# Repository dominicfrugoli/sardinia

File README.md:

<br/>
<div align="center">

<h3 align="center">Sardinia</h3>
<p align="center">
Sampler based on the Electrosmith Daisy platform

</p>
</div>

## About The Project

[Notion Project Homepage](https://fenidesign.notion.site/Sardinia-Independent-Project-24255e64caba44d3b6232d27743844be?pvs=4)

Sardinia is the codename for a sampler that is currently being built by me for an Independent Project during my senior year at Columbia College Chicago. It uses the Electrosmith Daisy platform and is an exercise for me to venture into the world of product design.

This independent project is called "The Product Design Process for Electronic Instruments" and was pitched by myself specifically to give myself experience in the process of the full production of an audio hardware device. This means starting at research, then going through every stage of production and design to end up with a final product. There is a large emphasis on the process and showing future companies that I understand somewhat what it takes.
### Built With

- [Daisy Seed](https://electro-smith.com/products/daisy-seed)
- [libDaisy](https://github.com/electro-smith/libDaisy)
- [DaisySP](https://github.com/electro-smith/DaisySP)
- [KiCad](https://www.kicad.org/)
- [Fusion 360](https://www.autodesk.com/products/fusion-360/)
## Roadmap

##### Weeks 1-5 | Ideation and Programming

- Week 1
    - Come up with overall idea and mission statement for the instrument
    - Research DSP ideas and programming concepts needed
    - Gather ideas and inspiration from specific hardware
- Week 2 & 3
    - Start programming all DSP and hardware handling for instrument
    - Lots of iteration and testing will be needed
    - Research here is critical as well to get main audio concepts down
    - Daisy Examples will be main research source
    - Recording different iterations of the project will be great for documentation
- Week 4 & 5
    - Work on finalizing code and getting it to a point for implementation
    - Use daisy examples and others’ code to help with style guidance
    - Get friends to test out for playability and sound, as well as get ideas
    - Build a central repo for code which can be updated as needed
    - Coding doesn’t stop with this step, but it should be mostly done by now
    - Start recording breadboard schematics if time allows to make PCB design easier

#####  Weeks 6-10 | PCB and Hardware Design

- Week 6 & 7
    - Refresh KICAD skills with tutorials
    - Build out schematic for PCB in KICAD
    - Design PCB completely and order for testing in week 8 & 9
    - Case design will be important here to make sure layout works with PCB
    - Final component selection will take place here
- Week 8 & 9
    - Work on case design with cardboard PCB to test out everything
    - Decide on case material (likely 3D printed)
    - Build out specifics for case such as standoff points and strength areas
    - Allow case to have daisy in a place that is easily reprogrammed
    - Assemble and test PCBs once they arrive (make changes and reorder if necessary)
    - Finish working on design and model for case
- Week 10
    - Start putting together first prototype of instrument with printed PCB and case
    - Play with instrument musically and have others try
    - This is when a lot of testing can be done for the usability

#####  Weeks 11-15 | Manufacturing and Documentation

- Week 11
    - Finalize design of case and overall visual style of instrument
    - Work on process for assembling, as well as BOM and any other assembly materials
- Week 12 & 13
    - Work on customer documentation for instrument
    - Design manual for the user
    - Design packaging for the instrument
    - Work on advertising and marketing for it
- Week 14 & 15
    - Build final version of instrument to be shown and displayed
        - Maybe one fully complete and two hollow cases for ad campaign
    - Final write up and documentation for instrument
    - Add writeup to portfolio website
    - Present it to friends and professors
    - Any last requirements for Visda

## Contact

Dominic Frugoli - [Portfolio](https://www.dominicfrugoli.com/) - dominicfrugoli@gmail.com

Project Link: [Notion Page](https://fenidesign.notion.site/Sardinia-Independent-Project-24255e64caba44d3b6232d27743844be?pvs=4)
## Acknowledgments

- Dr. Visda Goudarzi

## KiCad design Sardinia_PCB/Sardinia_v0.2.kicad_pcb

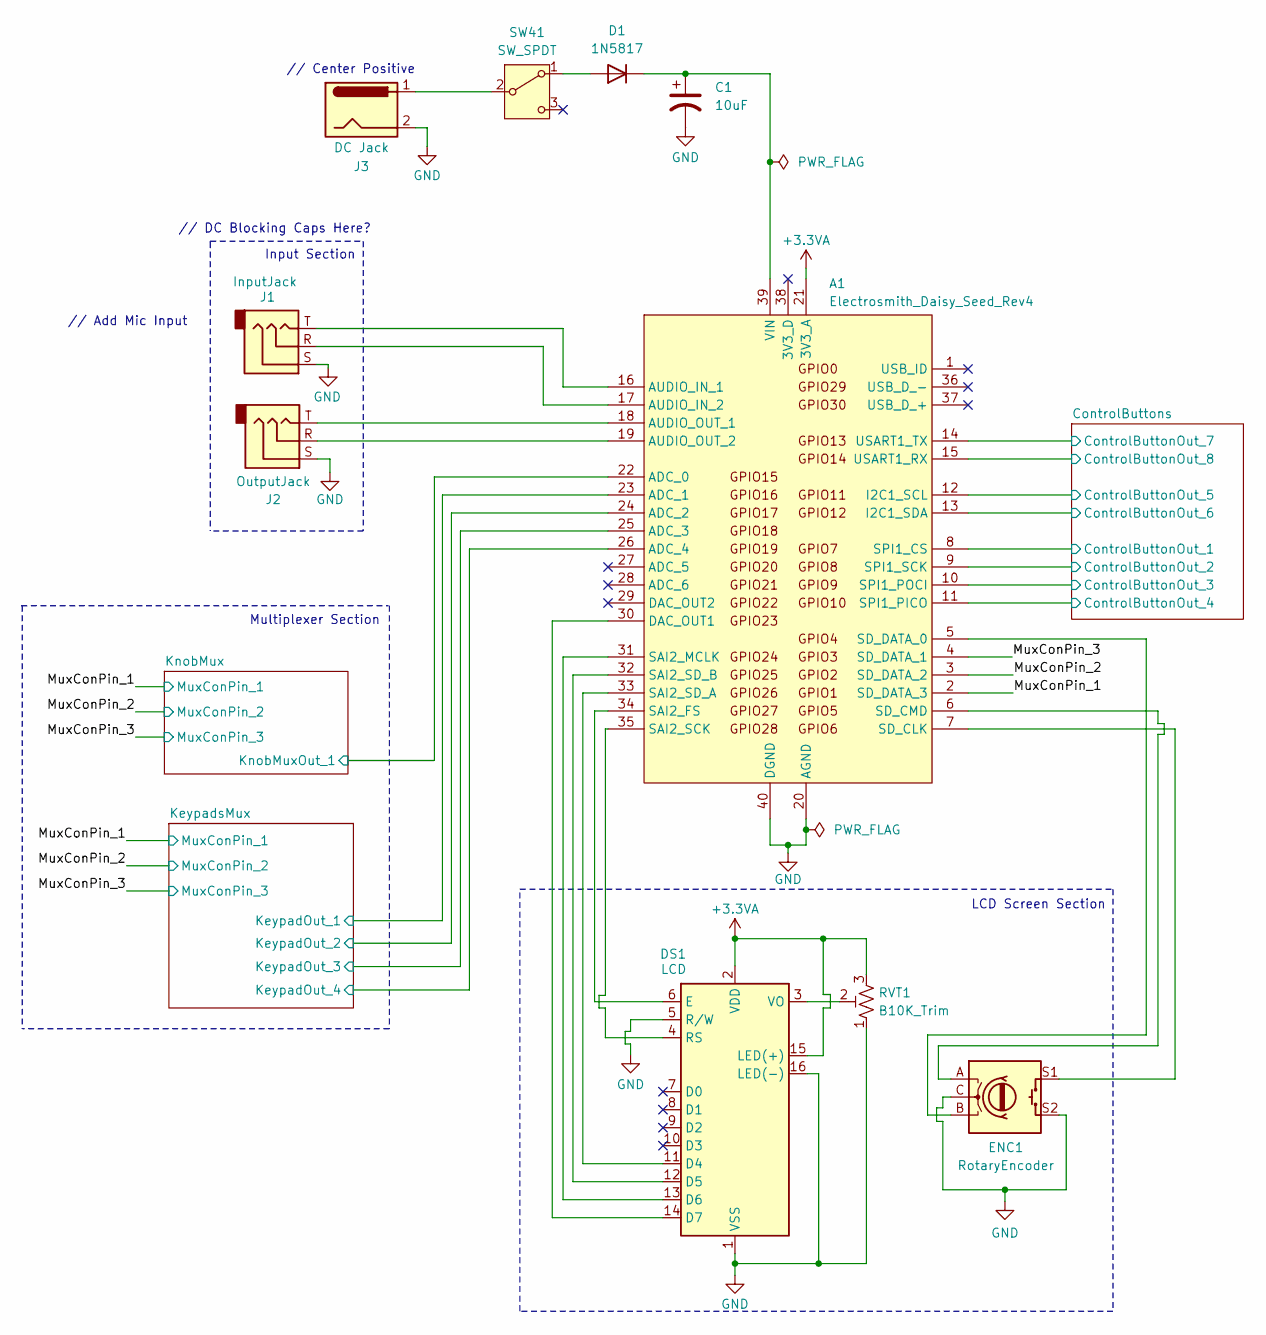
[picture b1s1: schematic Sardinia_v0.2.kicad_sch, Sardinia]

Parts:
A1: Electrosmith_Daisy_Seed_Rev4; Electrosmith_Daisy_Seed
C1: 10uF; CP_Radial_D5.0mm_P2.50mm
D1: 1N5817; D_DO-41_SOD81_P7.62mm_Horizontal
DS1: LCD; WC1602A
ENC1: RotaryEncoder; RotaryEncoder_Alps_EC11E-Switch_Vertical_H20mm
J1: InputJack; Jack_6.35mm_Neutrik_NMJ6HCD2_Horizontal
J2: OutputJack; Jack_6.35mm_Neutrik_NMJ6HCD2_Horizontal
J3: DC Jack; BarrelJack_Horizontal
RVT1: B10K_Trim; Potentiometer_Runtron_RM-065_Vertical
SW41: SW_SPDT; JST_PH_B3B-PH-K_1x03_P2.00mm_Vertical

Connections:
+3.3VA: A1.21 (3V3_A), DS1.2 (VDD), DS1.15 (LED(+)), RVT1.3; also elsewhere on the board
/ControlButtons/ControlButtonOut_1: A1.8 (SPI1_CS); also elsewhere on the board
/ControlButtons/ControlButtonOut_2: A1.9 (SPI1_SCK); also elsewhere on the board
/ControlButtons/ControlButtonOut_3: A1.10 (SPI1_POCI); also elsewhere on the board
/ControlButtons/ControlButtonOut_4: A1.11 (SPI1_PICO); also elsewhere on the board
/ControlButtons/ControlButtonOut_5: A1.12 (I2C1_SCL); also elsewhere on the board
/ControlButtons/ControlButtonOut_6: A1.13 (I2C1_SDA); also elsewhere on the board
/ControlButtons/ControlButtonOut_7: A1.14 (USART1_TX); also elsewhere on the board
/ControlButtons/ControlButtonOut_8: A1.15 (USART1_RX); also elsewhere on the board
/KeypadsMux/KeypadOut_1: A1.23 (ADC_1); also elsewhere on the board
/KeypadsMux/KeypadOut_2: A1.24 (ADC_2); also elsewhere on the board
/KeypadsMux/KeypadOut_3: A1.25 (ADC_3); also elsewhere on the board
/KeypadsMux/KeypadOut_4: A1.26 (ADC_4); also elsewhere on the board
/KnobMux/KnobMuxOut_1: A1.22 (ADC_0); also elsewhere on the board
/MuxConPin_1: A1.2 (SD_DATA_3); also elsewhere on the board
/MuxConPin_2: A1.3 (SD_DATA_2); also elsewhere on the board
/MuxConPin_3: A1.4 (SD_DATA_1); also elsewhere on the board
GND: A1.20 (AGND), A1.40 (DGND), C1.2, DS1.1 (VSS), DS1.5 (R/W), DS1.16 (LED(-)), ENC1.C, ENC1.S2, J1.S, J2.S, J3.2, RVT1.1; also elsewhere on the board
unnamed: A1.16 (AUDIO_IN_1), J1.T
unnamed: A1.17 (AUDIO_IN_2), J1.R
unnamed: A1.18 (AUDIO_OUT_1), J2.T
unnamed: A1.19 (AUDIO_OUT_2), J2.R
unnamed: A1.30 (DAC_OUT1), DS1.14 (D7)
unnamed: A1.34 (SAI2_FS), DS1.6 (E)
unnamed: A1.31 (SAI2_MCLK), DS1.13 (D6)
unnamed: A1.35 (SAI2_SCK), DS1.4 (RS)
unnamed: A1.33 (SAI2_SD_A), DS1.11 (D4)
unnamed: A1.32 (SAI2_SD_B), DS1.12 (D5)
unnamed: A1.7 (SD_CLK), ENC1.S1
unnamed: A1.6 (SD_CMD), ENC1.A
unnamed: A1.5 (SD_DATA_0), ENC1.B
unnamed: A1.39 (VIN), C1.1, D1.1 (K)
unnamed: D1.2 (A), SW41.1 (A)
unnamed: DS1.3 (VO), RVT1.2
unnamed: J3.1, SW41.2 (B)

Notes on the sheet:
// Center Positive
// Add Mic Input
LCD Screen Section
Input Section
// DC Blocking Caps Here?
Multiplexer Section

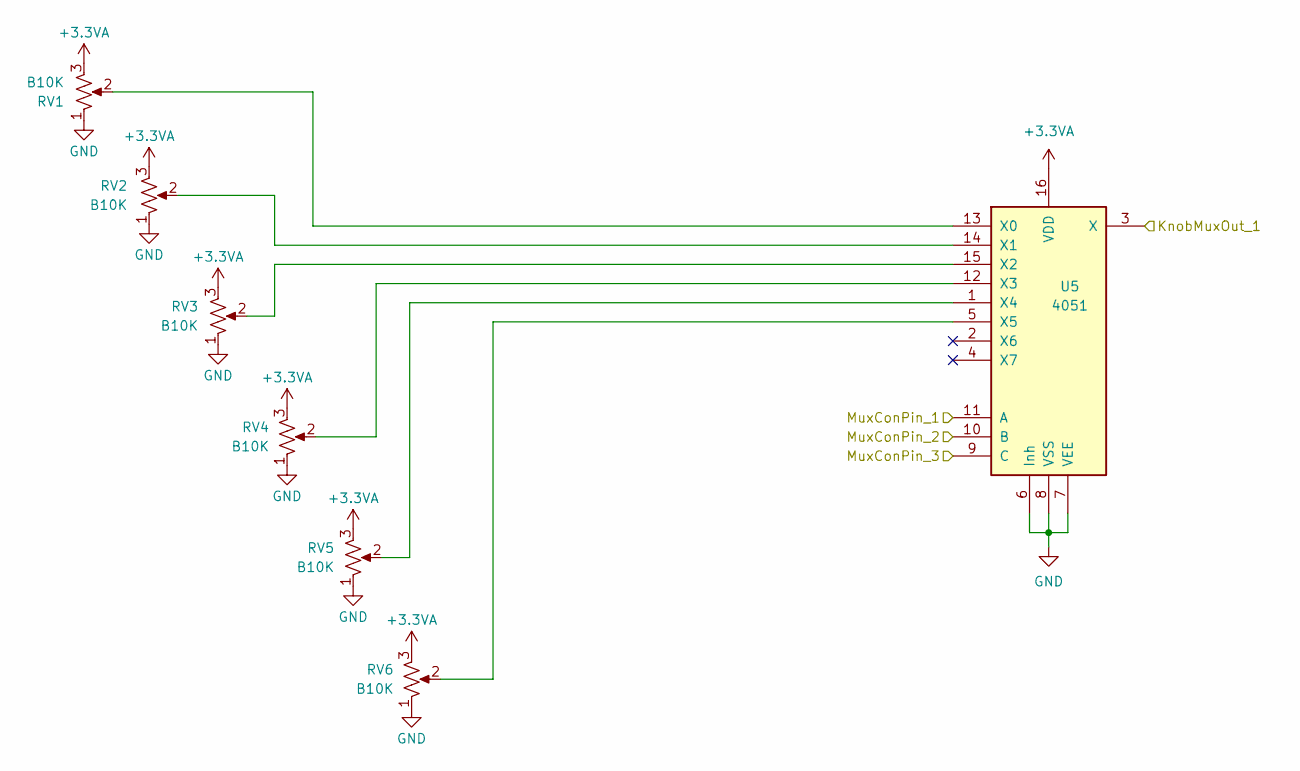
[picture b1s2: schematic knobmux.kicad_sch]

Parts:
RV1, RV2, RV3, RV4, RV5, RV6: B10K; Potentiometer_Alpha_RD901F-40-00D_Single_Vertical
U5: 4051; DIP-16_W7.62mm_LongPads

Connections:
+3.3VA: RV1.3, RV2.3, RV3.3, RV4.3, RV5.3, RV6.3, U5.16 (VDD); also elsewhere on the board
/KnobMux/KnobMuxOut_1: U5.3 (X); also elsewhere on the board
/MuxConPin_1: U5.11 (A); also elsewhere on the board
/MuxConPin_2: U5.10 (B); also elsewhere on the board
/MuxConPin_3: U5.9 (C); also elsewhere on the board
GND: RV1.1, RV2.1, RV3.1, RV4.1, RV5.1, RV6.1, U5.6 (Inh), U5.7 (VEE), U5.8 (VSS); also elsewhere on the board
unnamed: RV1.2, U5.13 (X0)
unnamed: RV2.2, U5.14 (X1)
unnamed: RV3.2, U5.15 (X2)
unnamed: RV4.2, U5.12 (X3)
unnamed: RV5.2, U5.1 (X4)
unnamed: RV6.2, U5.5 (X5)

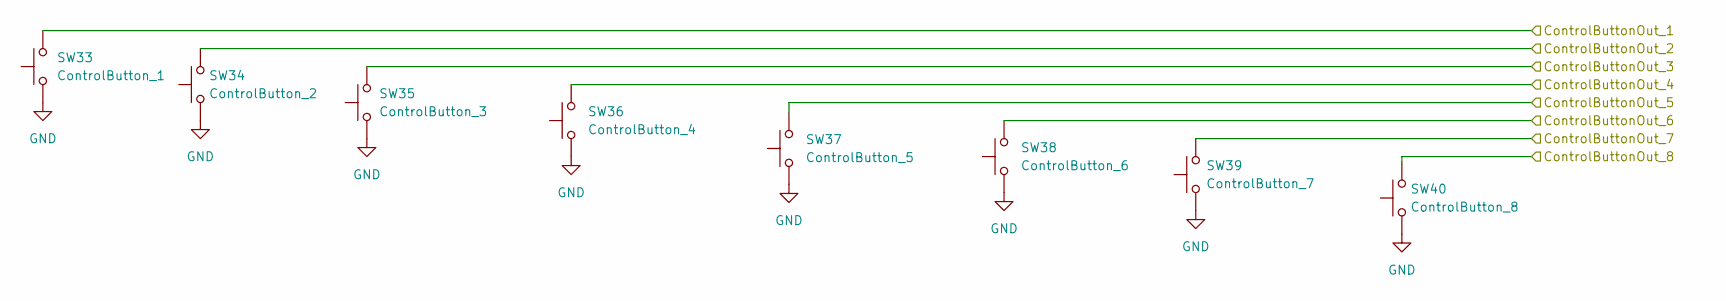
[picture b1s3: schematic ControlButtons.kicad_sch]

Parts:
SW33: ControlButton_1; SW_Cherry_MX_1.00u_PCB
SW34: ControlButton_2; SW_Cherry_MX_1.00u_PCB
SW35: ControlButton_3; SW_Cherry_MX_1.00u_PCB
SW36: ControlButton_4; SW_Cherry_MX_1.00u_PCB
SW37: ControlButton_5; SW_Cherry_MX_1.00u_PCB
SW38: ControlButton_6; SW_Cherry_MX_1.00u_PCB
SW39: ControlButton_7; SW_Cherry_MX_1.00u_PCB
SW40: ControlButton_8; SW_Cherry_MX_1.00u_PCB

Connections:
/ControlButtons/ControlButtonOut_1: SW33.2; also elsewhere on the board
/ControlButtons/ControlButtonOut_2: SW34.2; also elsewhere on the board
/ControlButtons/ControlButtonOut_3: SW35.2; also elsewhere on the board
/ControlButtons/ControlButtonOut_4: SW36.2; also elsewhere on the board
/ControlButtons/ControlButtonOut_5: SW37.2; also elsewhere on the board
/ControlButtons/ControlButtonOut_6: SW38.2; also elsewhere on the board
/ControlButtons/ControlButtonOut_7: SW39.2; also elsewhere on the board
/ControlButtons/ControlButtonOut_8: SW40.2; also elsewhere on the board
GND: SW33.1, SW34.1, SW35.1, SW36.1, SW37.1, SW38.1, SW39.1, SW40.1; also elsewhere on the board

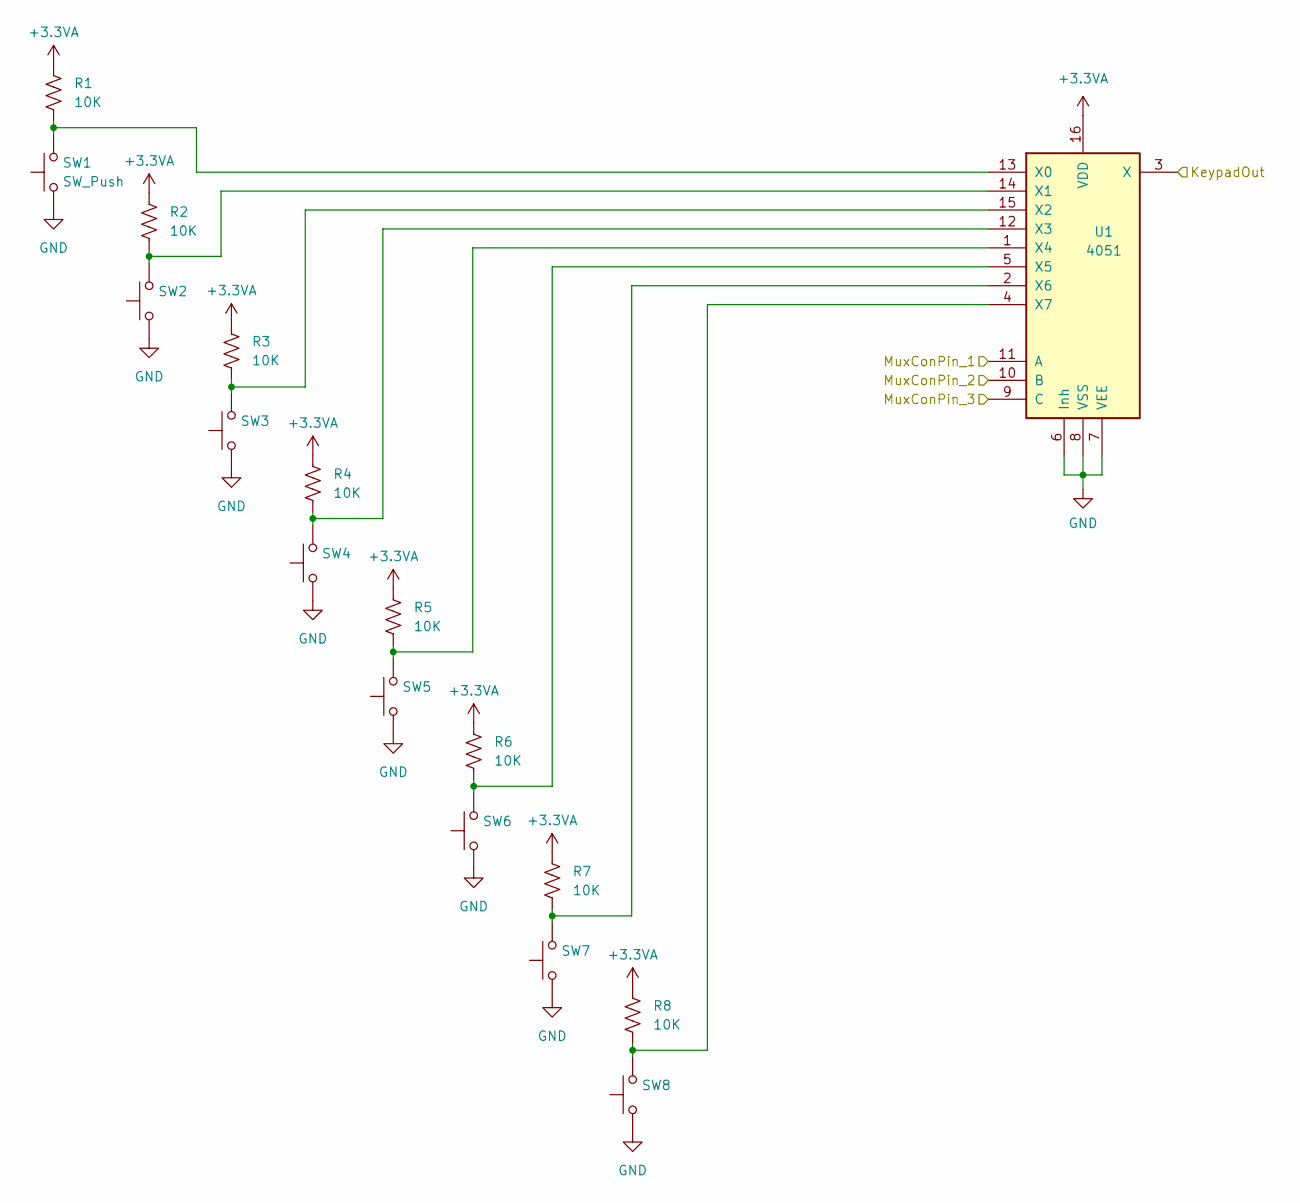
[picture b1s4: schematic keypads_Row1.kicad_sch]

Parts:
R1, R2, R3, R4, R5, R6, R7, R8: 10K; R_1206_3216Metric_Pad1.30x1.75mm_HandSolder
SW1, SW2, SW3, SW4, SW5, SW6, SW7, SW8: SW_Push; PG1350
U1: 4051; DIP-16_W7.62mm_LongPads

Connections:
+3.3VA: R1.1, R2.1, R3.1, R4.1, R5.1, R6.1, R7.1, R8.1, U1.16 (VDD); also elsewhere on the board
/KeypadsMux/KeypadOut_1: U1.3 (X); also elsewhere on the board
/MuxConPin_1: U1.11 (A); also elsewhere on the board
/MuxConPin_2: U1.10 (B); also elsewhere on the board
/MuxConPin_3: U1.9 (C); also elsewhere on the board
GND: SW1.1, SW2.1, SW3.1, SW4.1, SW5.1, SW6.1, SW7.1, SW8.1, U1.6 (Inh), U1.7 (VEE), U1.8 (VSS); also elsewhere on the board
unnamed: R1.2, SW1.2, U1.13 (X0)
unnamed: R2.2, SW2.2, U1.14 (X1)
unnamed: R3.2, SW3.2, U1.15 (X2)
unnamed: R4.2, SW4.2, U1.12 (X3)
unnamed: R5.2, SW5.2, U1.1 (X4)
unnamed: R6.2, SW6.2, U1.5 (X5)
unnamed: R7.2, SW7.2, U1.2 (X6)
unnamed: R8.2, SW8.2, U1.4 (X7)

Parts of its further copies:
R9, R10, R11, R12, R13, R14, R15, R16, R17, R18, R19, R20, R21, R22, R23, R24, R25, R26, R27, R28, R29, R30, R31, R32: 10K; R_1206_3216Metric_Pad1.30x1.75mm_HandSolder
SW9, SW10, SW11, SW12, SW13, SW14, SW15, SW16, SW17, SW18, SW19, SW20, SW21, SW22, SW23, SW24, SW25, SW26, SW27, SW28, SW29, SW30, SW31, SW32: SW_Push; PG1350
U2, U3, U4: 4051; DIP-16_W7.62mm_LongPads

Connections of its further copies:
+3.3VA: R9.1, R10.1, R11.1, R12.1, R13.1, R14.1, R15.1, R16.1, R17.1, R18.1, R19.1, R20.1, R21.1, R22.1, R23.1, R24.1, R25.1, R26.1, R27.1, R28.1, R29.1, R30.1, R31.1, R32.1, U2.16 (VDD), U3.16 (VDD), U4.16 (VDD); also elsewhere on the board
/KeypadsMux/KeypadOut_2: U2.3 (X); also elsewhere on the board
/KeypadsMux/KeypadOut_3: U3.3 (X); also elsewhere on the board
/KeypadsMux/KeypadOut_4: U4.3 (X); also elsewhere on the board
/MuxConPin_1: U2.11 (A), U3.11 (A), U4.11 (A); also elsewhere on the board
/MuxConPin_2: U2.10 (B), U3.10 (B), U4.10 (B); also elsewhere on the board
/MuxConPin_3: U2.9 (C), U3.9 (C), U4.9 (C); also elsewhere on the board
GND: SW9.1, SW10.1, SW11.1, SW12.1, SW13.1, SW14.1, SW15.1, SW16.1, SW17.1, SW18.1, SW19.1, SW20.1, SW21.1, SW22.1, SW23.1, SW24.1, SW25.1, SW26.1, SW27.1, SW28.1, SW29.1, SW30.1, SW31.1, SW32.1, U2.6 (Inh), U2.7 (VEE), U2.8 (VSS), U3.6 (Inh), U3.7 (VEE), U3.8 (VSS), U4.6 (Inh), U4.7 (VEE), U4.8 (VSS); also elsewhere on the board
unnamed: R9.2, SW9.2, U2.13 (X0)
unnamed: R10.2, SW10.2, U2.14 (X1)
unnamed: R11.2, SW11.2, U2.15 (X2)
unnamed: R12.2, SW12.2, U2.12 (X3)
unnamed: R13.2, SW13.2, U2.1 (X4)
unnamed: R14.2, SW14.2, U2.5 (X5)
unnamed: R15.2, SW15.2, U2.2 (X6)
unnamed: R16.2, SW16.2, U2.4 (X7)
unnamed: R17.2, SW17.2, U3.13 (X0)
unnamed: R18.2, SW18.2, U3.14 (X1)
unnamed: R19.2, SW19.2, U3.15 (X2)
unnamed: R20.2, SW20.2, U3.12 (X3)
unnamed: R21.2, SW21.2, U3.1 (X4)
unnamed: R22.2, SW22.2, U3.5 (X5)
unnamed: R23.2, SW23.2, U3.2 (X6)
unnamed: R24.2, SW24.2, U3.4 (X7)
unnamed: R25.2, SW25.2, U4.13 (X0)
unnamed: R26.2, SW26.2, U4.14 (X1)
unnamed: R27.2, SW27.2, U4.15 (X2)
unnamed: R28.2, SW28.2, U4.12 (X3)
unnamed: R29.2, SW29.2, U4.1 (X4)
unnamed: R30.2, SW30.2, U4.5 (X5)
unnamed: R31.2, SW31.2, U4.2 (X6)
unnamed: R32.2, SW32.2, U4.4 (X7)

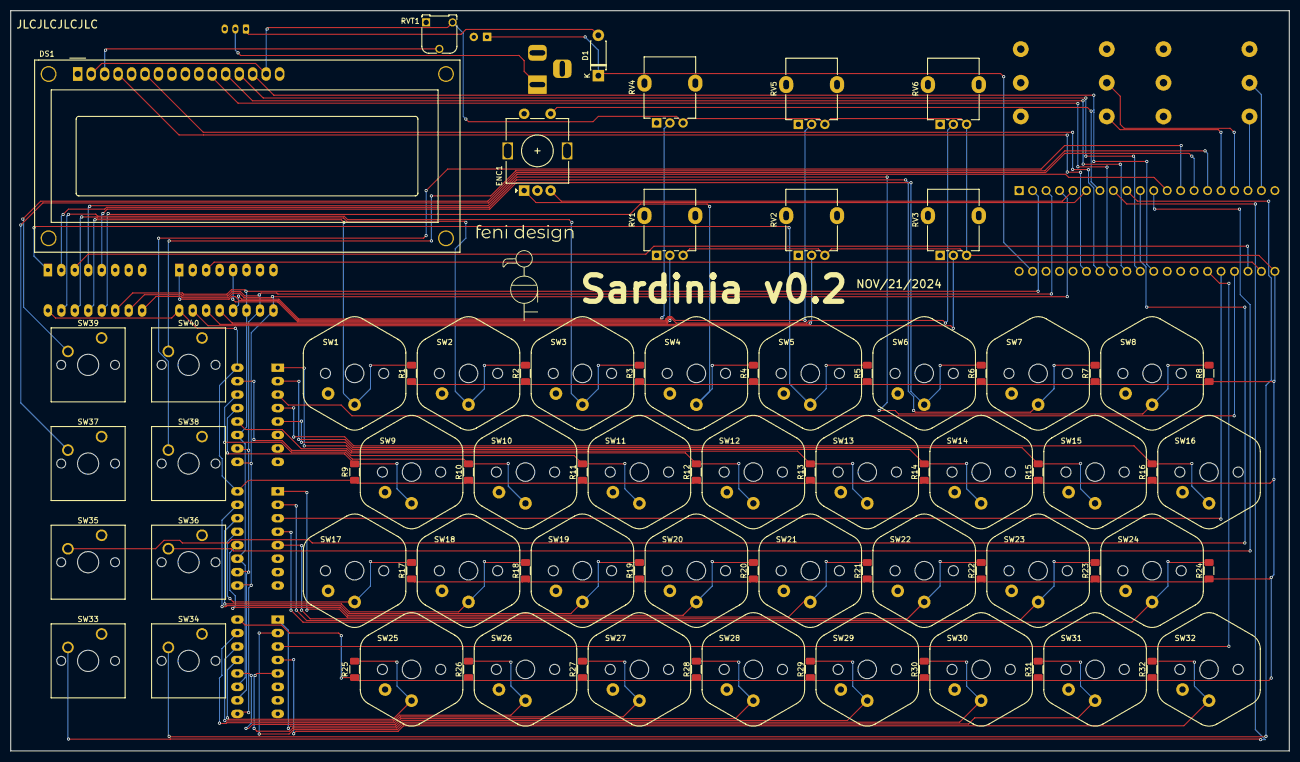
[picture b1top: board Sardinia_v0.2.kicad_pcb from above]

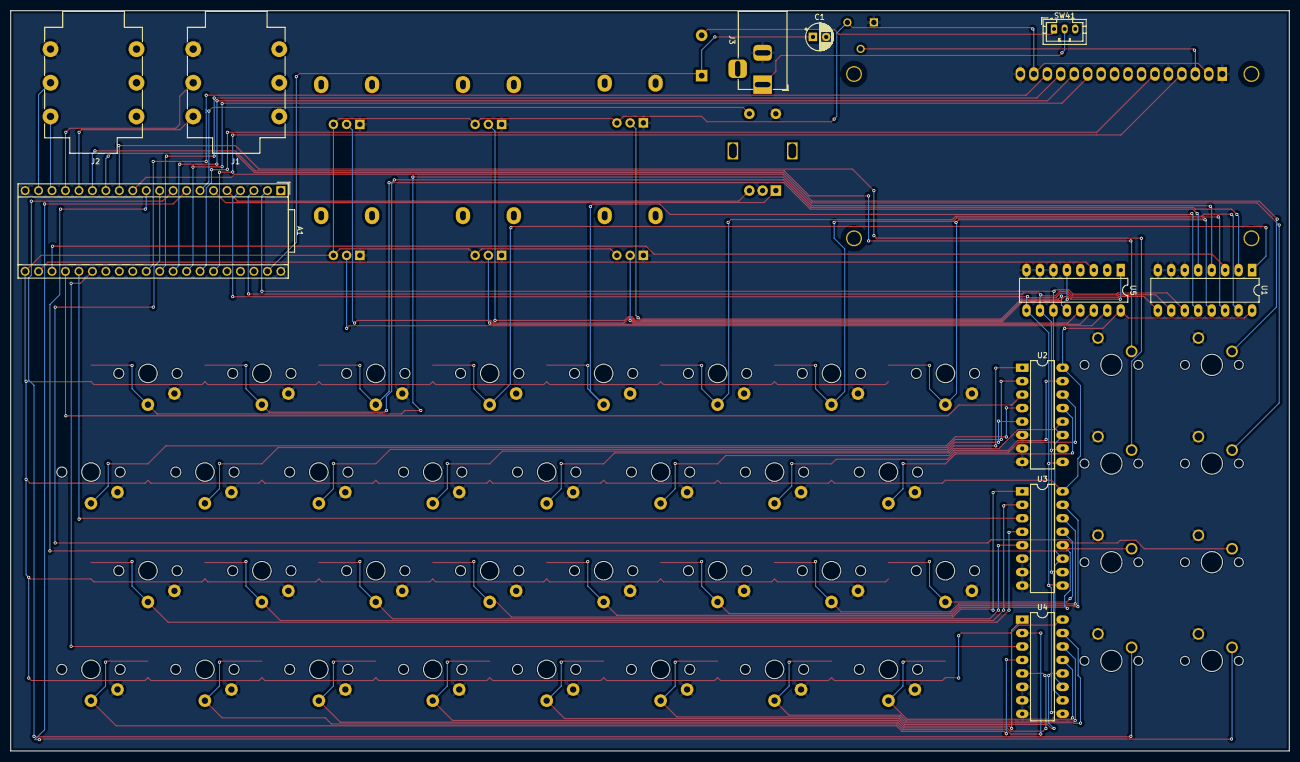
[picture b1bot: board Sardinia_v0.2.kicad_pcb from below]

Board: 4 copper layers, 241.3 x 139.7 mm, 93 parts (11 on the bottom side), 73 nets.

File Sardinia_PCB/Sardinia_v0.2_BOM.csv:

"Id";"Designator";"Footprint";"Quantity";"Designation";"Supplier and ref";
1;"R10,R24,R22,R31,R1,R17,R27,R21,R12,R19,R14,R3,R25,R9,R11,R7,R6,R18,R8,R26,R13,R30,R29,R15,R32,R23,R4,R16,R2,R5,R28,R20";"R_1206_3216Metric_Pad1.30x1.75mm_HandSolder";32;"10K";;;
2;"RV3,RV1,RV6,RV5,RV4,RV2";"Potentiometer_Alpha_RD901F-40-00D_Single_Vertical";6;"B10K";;;
3;"SW34";"SW_Cherry_MX_1.00u_PCB";1;"ControlButton_2";;;
4;"SW14,SW10,SW3,SW30,SW24,SW16,SW5,SW1,SW9,SW23,SW31,SW32,SW26,SW15,SW17,SW13,SW7,SW19,SW22,SW20,SW28,SW25,SW18,SW4,SW29,SW27,SW8,SW12,SW2,SW21,SW6,SW11";"PG1350";32;"SW_Push";;;
5;"RVT1";"Potentiometer_Runtron_RM-065_Vertical";1;"B10K_Trim";;;
6;"SW35";"SW_Cherry_MX_1.00u_PCB";1;"ControlButton_3";;;
7;"D1";"D_DO-41_SOD81_P7.62mm_Horizontal";1;"1N5817";;;
8;"SW39";"SW_Cherry_MX_1.00u_PCB";1;"ControlButton_7";;;
9;"ENC1";"RotaryEncoder_Alps_EC11E-Switch_Vertical_H20mm";1;"RotaryEncoder";;;
10;"SW40";"SW_Cherry_MX_1.00u_PCB";1;"ControlButton_8";;;
11;"DS1";"WC1602A";1;"LCD";;;
12;"SW33";"SW_Cherry_MX_1.00u_PCB";1;"ControlButton_1";;;
13;"SW37";"SW_Cherry_MX_1.00u_PCB";1;"ControlButton_5";;;
14;"SW38";"SW_Cherry_MX_1.00u_PCB";1;"ControlButton_6";;;
15;"SW36";"SW_Cherry_MX_1.00u_PCB";1;"ControlButton_4";;;
16;"J3";"BarrelJack_Horizontal";1;"DC Jack";;;
17;"J2";"Jack_6.35mm_Neutrik_NMJ6HCD2_Horizontal";1;"OutputJack";;;
18;"J1";"Jack_6.35mm_Neutrik_NMJ6HCD2_Horizontal";1;"InputJack";;;
19;"C1";"CP_Radial_D5.0mm_P2.50mm";1;"10uF";;;
20;"SW41";"JST_PH_B3B-PH-K_1x03_P2.00mm_Vertical";1;"SW_SPDT";;;
21;"U5,U4,U3,U2,U1";"DIP-16_W7.62mm_LongPads";5;"4051";;;
22;"A1";"Electrosmith_Daisy_Seed";1;"Electrosmith_Daisy_Seed_Rev4";;;

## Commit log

2024-10-08 added libraries
2024-10-08 last initial commit
2024-10-23 PCB hardware and sampler work
    Updated all the hardware handling to fit with the prototype PCB and implemented some parts of the sampler algorithm (not working yet)
2024-10-29 Storing Splices and Two Modes
    Implemented storing audio splices into a buffer for playback (as well as general recording and playback improvements). Also changed to a two mode system (record and play).
2024-10-29 Update README.md
    Added link notion project page
2024-10-29 Basic implementation of effects
2024-10-30 Play Mode First Implementation
2024-11-07 Eliminated play and record buttons (legacy code)
2024-11-07 Update .gitignore to remove unwanted files
2024-11-07 Changed gitignore
2024-12-11 Changed Control Buttons Code
    Control Buttons on new PCB don't go through a MUX. They go directly to the MCU so I removed the code that manually checked for rising edge/falling edge. I used the built in Switch class for it instea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
2025-01-31 Added KiCad files
